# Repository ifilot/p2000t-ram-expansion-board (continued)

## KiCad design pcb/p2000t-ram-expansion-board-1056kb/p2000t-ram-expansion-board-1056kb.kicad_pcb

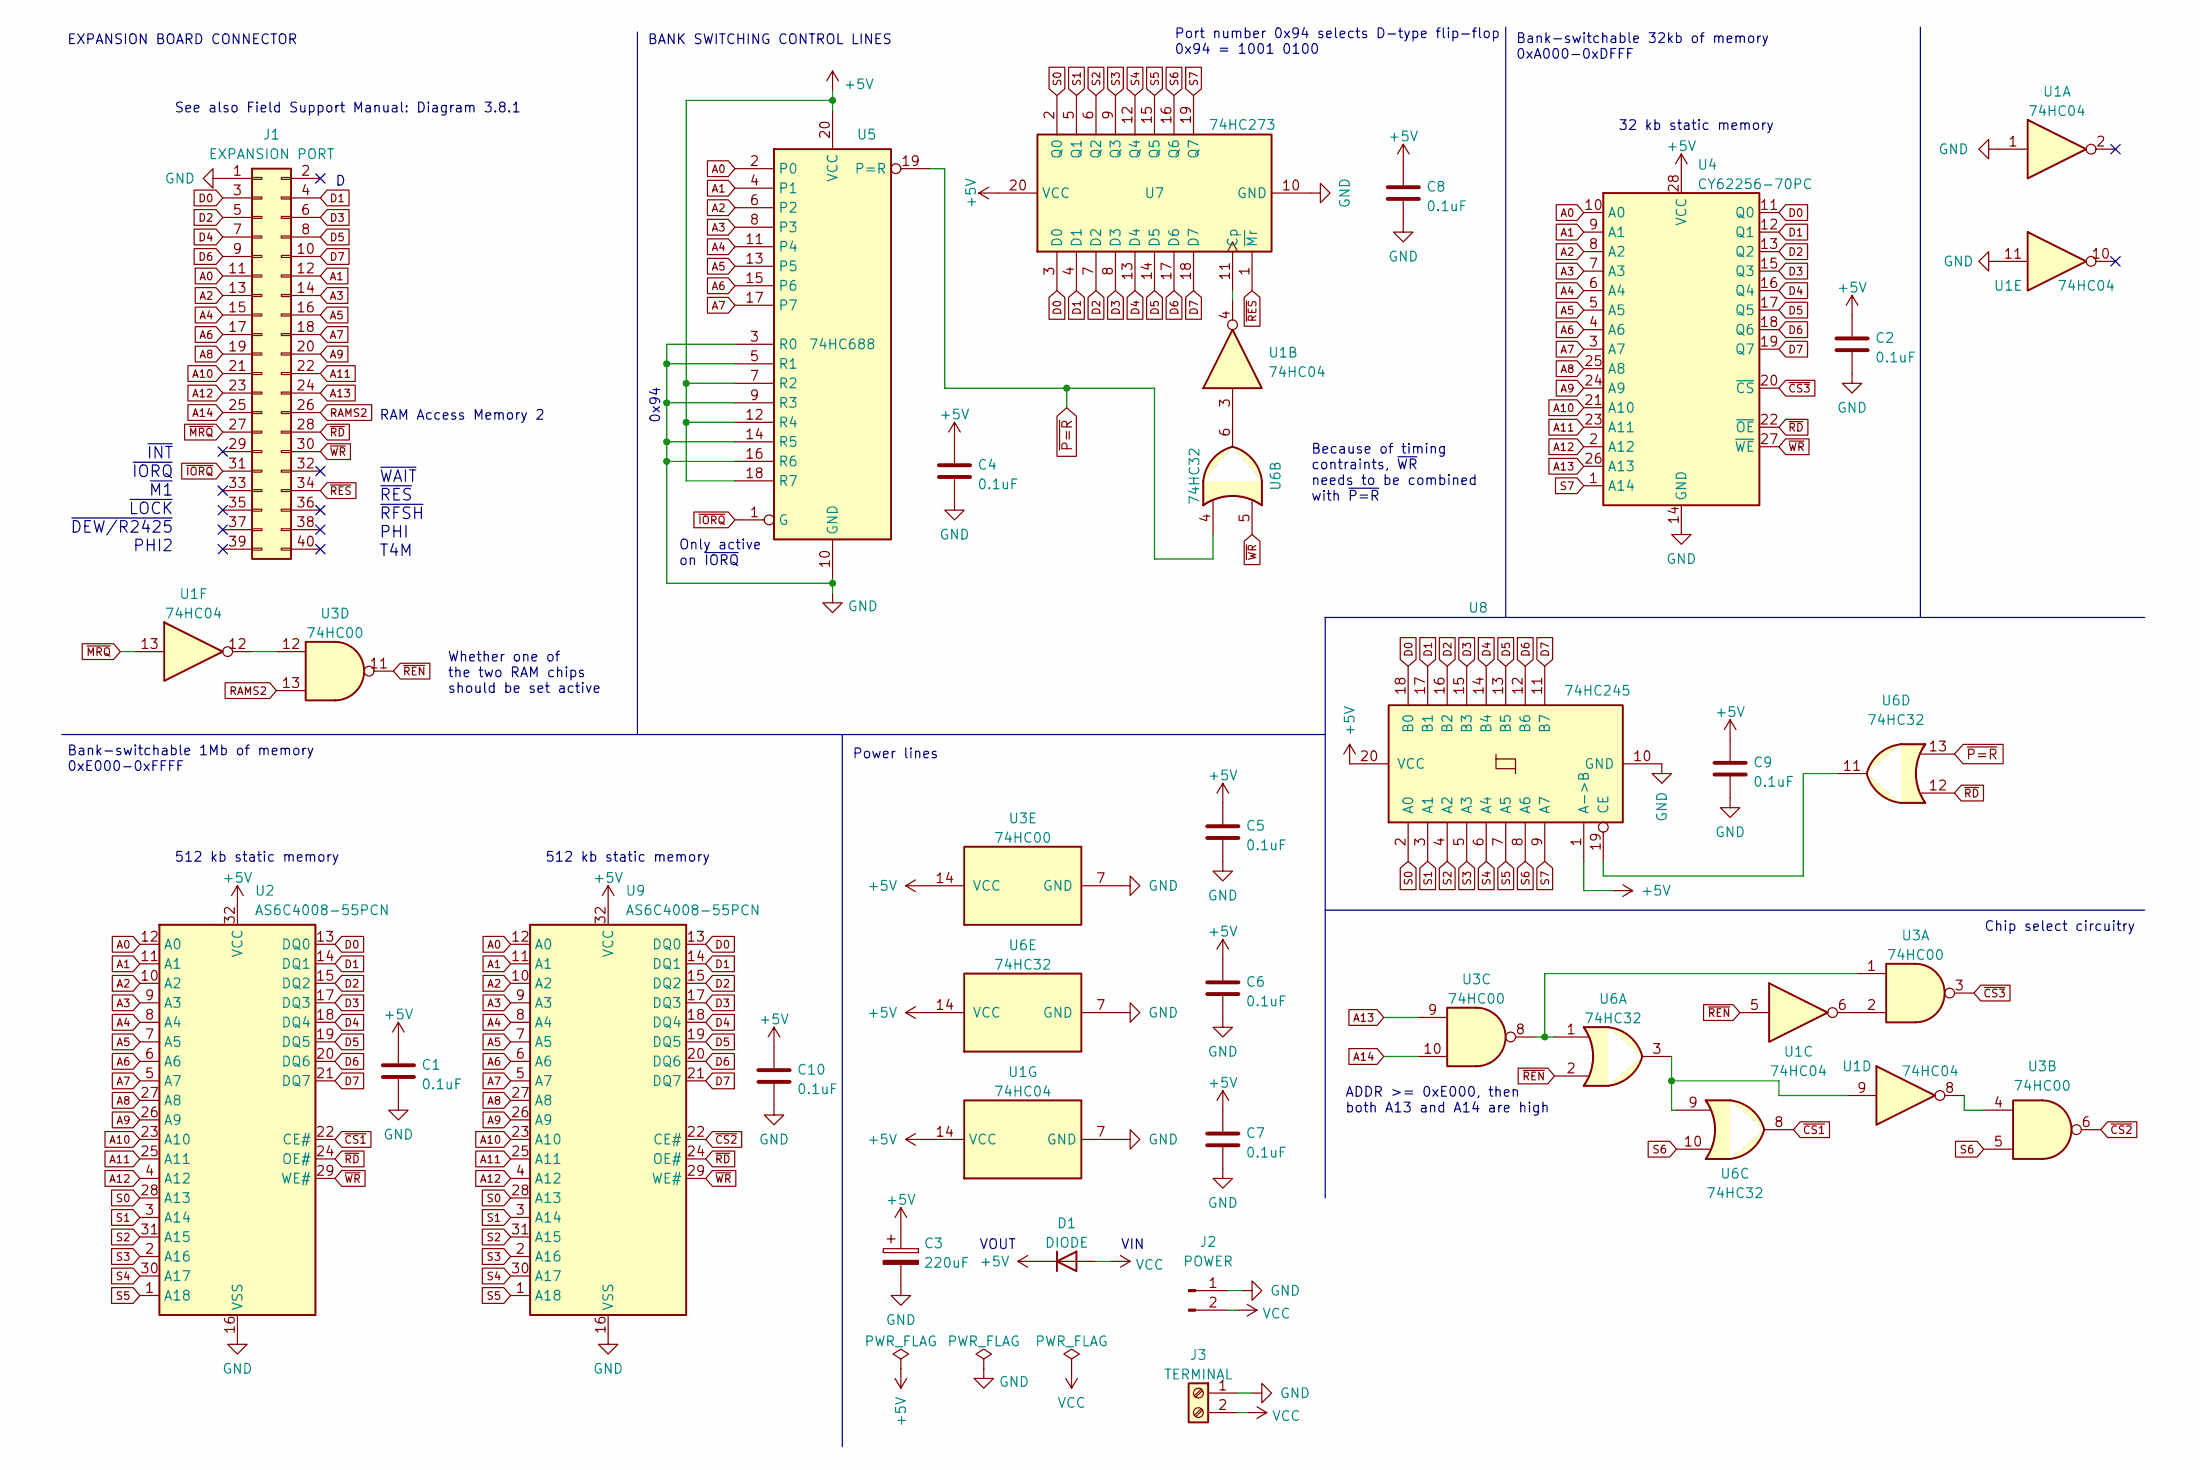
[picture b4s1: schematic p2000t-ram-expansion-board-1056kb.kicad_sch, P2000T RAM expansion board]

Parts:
C1, C2, C4, C5, C6, C7, C8, C9, C10: 0.1uF; C_Disc_D5.0mm_W2.5mm_P5.00mm
C3: 220uF; CP_Radial_D6.3mm_P2.50mm
D1: DIODE; D_DO-35_SOD27_P7.62mm_Horizontal
J1: EXPANSION PORT; PinHeader_2x20_P2.54mm_Vertical
J2: POWER; PinHeader_1x02_P2.54mm_Vertical
J3: TERMINAL; TerminalBlock_bornier-2_P5.08mm
U1: 74HC04; DIP-14_W7.62mm_Socket
U2, U9: AS6C4008-55PCN; DIP-32_W15.24mm_Socket
U3: 74HC00; DIP-14_W7.62mm_Socket
U4: CY62256-70PC; DIP-28_W15.24mm_Socket
U5: 74HC688; DIP-20_W7.62mm_Socket
U6: 74HC32; DIP-14_W7.62mm_Socket
U7: 74HC273; DIP-20_W7.62mm_Socket
U8: 74HC245; DIP-20_W7.62mm_Socket

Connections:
+5V: C1.1, C2.1, C3.1, C4.1, C5.1, C6.1, C7.1, C8.1, C9.1, C10.1, D1.1 (K), U1.14 (VCC), U2.32 (VCC), U3.14 (VCC), U4.28 (VCC), U5.7 (R2), U5.12 (R4), U5.18 (R7), U5.20 (VCC), U6.14 (VCC), U7.20 (VCC), U8.1 (A->B), U8.20 (VCC), U9.32 (VCC)
A0: J1.11, U2.12 (A0), U4.10 (A0), U5.2 (P0), U9.12 (A0)
A1: J1.12, U2.11 (A1), U4.9 (A1), U5.4 (P1), U9.11 (A1)
A2: J1.13, U2.10 (A2), U4.8 (A2), U5.6 (P2), U9.10 (A2)
A3: J1.14, U2.9 (A3), U4.7 (A3), U5.8 (P3), U9.9 (A3)
A4: J1.15, U2.8 (A4), U4.6 (A4), U5.11 (P4), U9.8 (A4)
A5: J1.16, U2.7 (A5), U4.5 (A5), U5.13 (P5), U9.7 (A5)
A6: J1.17, U2.6 (A6), U4.4 (A6), U5.15 (P6), U9.6 (A6)
A7: J1.18, U2.5 (A7), U4.3 (A7), U5.17 (P7), U9.5 (A7)
A8: J1.19, U2.27 (A8), U4.25 (A8), U9.27 (A8)
A9: J1.20, U2.26 (A9), U4.24 (A9), U9.26 (A9)
A10: J1.21, U2.23 (A10), U4.21 (A10), U9.23 (A10)
A11: J1.22, U2.25 (A11), U4.23 (A11), U9.25 (A11)
A12: J1.23, U2.4 (A12), U4.2 (A12), U9.4 (A12)
A13: J1.24, U3.9, U4.26 (A13)
A14: J1.25, U3.10
D0: J1.3, U2.13 (DQ0), U4.11 (Q0), U7.3 (D0), U8.18 (B0), U9.13 (DQ0)
D1: J1.4, U2.14 (DQ1), U4.12 (Q1), U7.4 (D1), U8.17 (B1), U9.14 (DQ1)
D2: J1.5, U2.15 (DQ2), U4.13 (Q2), U7.7 (D2), U8.16 (B2), U9.15 (DQ2)
D3: J1.6, U2.17 (DQ3), U4.15 (Q3), U7.8 (D3), U8.15 (B3), U9.17 (DQ3)
D4: J1.7, U2.18 (DQ4), U4.16 (Q4), U7.13 (D4), U8.14 (B4), U9.18 (DQ4)
D5: J1.8, U2.19 (DQ5), U4.17 (Q5), U7.14 (D5), U8.13 (B5), U9.19 (DQ5)
D6: J1.9, U2.20 (DQ6), U4.18 (Q6), U7.17 (D6), U8.12 (B6), U9.20 (DQ6)
D7: J1.10, U2.21 (DQ7), U4.19 (Q7), U7.18 (D7), U8.11 (B7), U9.21 (DQ7)
GND: C1.2, C2.2, C3.2, C4.2, C5.2, C6.2, C7.2, C8.2, C9.2, C10.2, J1.1, J2.1, J3.1, U1.1, U1.7 (GND), U1.11, U2.16 (VSS), U3.7 (GND), U4.14 (GND), U5.3 (R0), U5.5 (R1), U5.9 (R3), U5.10 (GND), U5.14 (R5), U5.16 (R6), U6.7 (GND), U7.10 (GND), U8.10 (GND), U9.16 (VSS)
unnamed: U1.3, U6.6
unnamed: U1.6, U3.2
unnamed: U1.8, U3.4
unnamed: U1.9, U6.3, U6.9
unnamed: U1.12, U3.12
unnamed: U3.1, U3.8, U6.1
unnamed: U1.4, U7.11 (Cp)
unnamed: U6.11, U8.19 (CE)
RAMS2: J1.26, U3.13
S0: U2.28 (A13), U7.2 (Q0), U8.2 (A0), U9.28 (A13)
S1: U2.3 (A14), U7.5 (Q1), U8.3 (A1), U9.3 (A14)
S2: U2.31 (A15), U7.6 (Q2), U8.4 (A2), U9.31 (A15)
S3: U2.2 (A16), U7.9 (Q3), U8.5 (A3), U9.2 (A16)
S4: U2.30 (A17), U7.12 (Q4), U8.6 (A4), U9.30 (A17)
S5: U2.1 (A18), U7.15 (Q5), U8.7 (A5), U9.1 (A18)
S6: U3.5, U6.10, U7.16 (Q6), U8.8 (A6)
S7: U4.1 (A14), U7.19 (Q7), U8.9 (A7)
VCC: D1.2 (A), J2.2, J3.2
~CS1: U2.22 (CE#), U6.8
~CS2: U3.6, U9.22 (CE#)
~CS3: U3.3, U4.20 (~CS)
~IORQ: J1.31, U5.1 (G)
~MRQ: J1.27, U1.13
~P=R: U5.19 (P=R), U6.4, U6.13
~RD: J1.28, U2.24 (OE#), U4.22 (~OE), U6.12, U9.24 (OE#)
~REN: U1.5, U3.11, U6.2
~RES: J1.34, U7.1 (~Mr)
~WR: J1.30, U2.29 (WE#), U4.27 (~WE), U6.5, U9.29 (WE#)

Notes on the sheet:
512 kb static memory
VIN
EXPANSION BOARD CONNECTOR
0x94
VOUT
32 kb static memory
~{INT} ~{IORQ} ~{M1} ~{LOCK} ~{DEW/R2425} PHI2
Only active on ~{IORQ}
RAM Access Memory 2
Bank-switchable 32kb of memory 0xA000-0xDFFF
Because of timing contraints, ~{WR} needs to be combined with ~{P=R}
Bank-switchable 1Mb of memory 0xE000-0xFFFF
See also Field Support Manual: Diagram 3.8.1
Power lines
Chip select circuitry
BANK SWITCHING CONTROL LINES
ADDR >= 0xE000, then both A13 and A14 are high
~{WAIT} ~{RES} ~{RFSH} PHI T4M
Whether one of the two RAM chips should be set active
Port number 0x94 selects D-type flip-flop 0x94 = 1001 0100

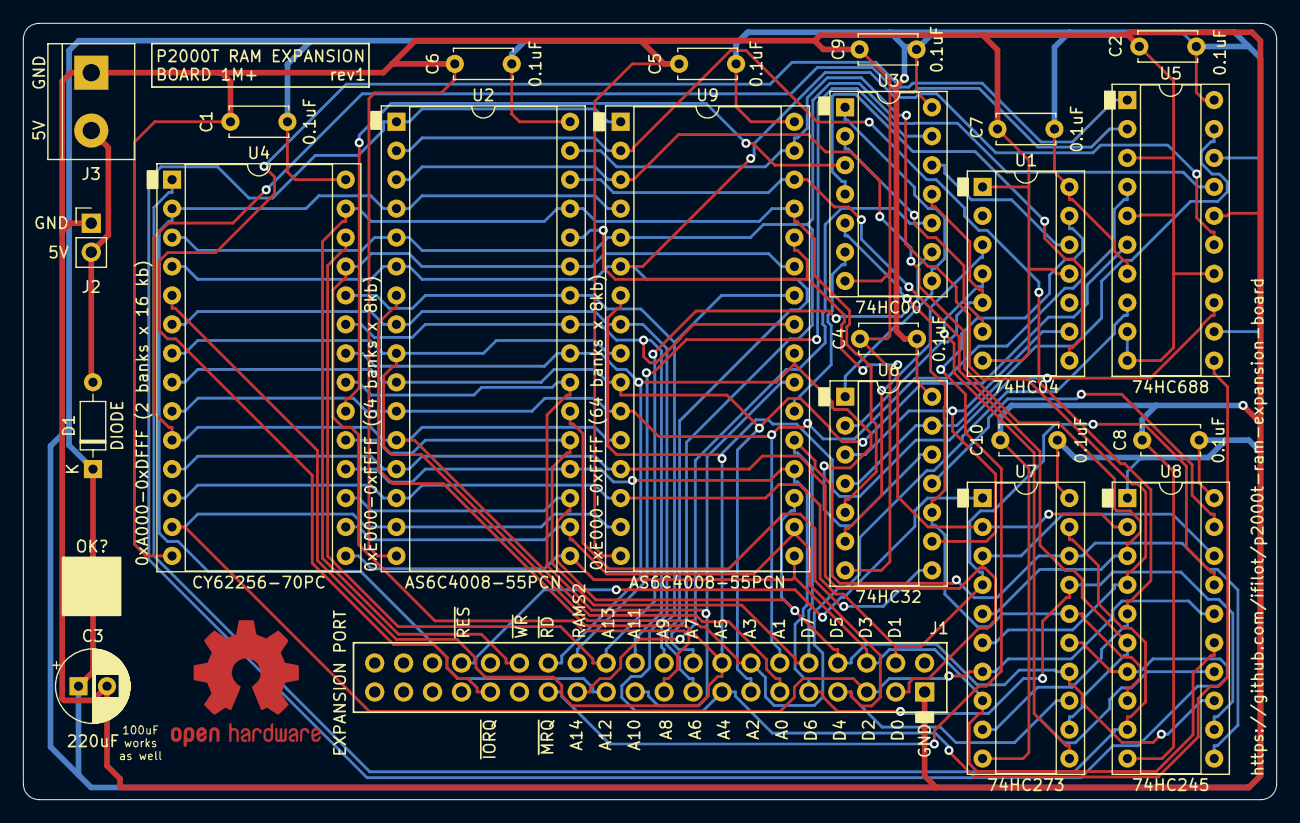
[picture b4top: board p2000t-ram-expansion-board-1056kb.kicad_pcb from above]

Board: 2 copper layers, 110.0 x 68.1 mm, 24 parts (1 on the bottom side), 53 nets.

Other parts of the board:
LOGO1: OSHW-Logo2_14.6x12mm_Copper_AND_Mask

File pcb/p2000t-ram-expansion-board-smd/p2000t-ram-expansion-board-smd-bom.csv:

Comment,Designator,Footprint,LCSC Part #
0.1uF Unpolarized capacitor,"C1,C2,C4,C5,C6,C7,C8,C9,C10",C_0805_2012Metric_Pad1.18x1.45mm_HandSolder,C49678
100uF Polarized capacitor,C3,CP_EIA-3528-21_Kemet-B_Pad1.50x2.35mm_HandSolder,C16133
DIODE Diode,D1,D_SOD-123,C81598
74HC04 Hex Inverter,U1,SOIC-14_3.9x8.7mm_P1.27mm,C5586
"CY62256-70PC 256K (32K x 8) Static RAM, 70ns, DIP-28","U2,U4",TSOP-I-28_11.8x8mm_P0.55mm,C2759940
74HC00 quad 2-input NAND gate,U3,SOIC-14_3.9x8.7mm_P1.27mm,C10090
74HC688 8-bit magnitude comparator,U5,SOIC-20W_7.5x12.8mm_P1.27mm,C88042
74HC32 Quad 2-input OR,U6,SOIC-14_3.9x8.7mm_P1.27mm,C5632
"74HC173 4-bit D-type Register, 3 state out",U7,SOIC-16_3.9x9.9mm_P1.27mm,C546651
"74HC245 Octal BUS Transceivers, 3-State outputs",U8,SOIC-20W_7.5x12.8mm_P1.27mm,C5625
74HC157 Quad 2 to 1 line Multiplexer,U9,SOIC-16_3.9x9.9mm_P1.27mm,C5609

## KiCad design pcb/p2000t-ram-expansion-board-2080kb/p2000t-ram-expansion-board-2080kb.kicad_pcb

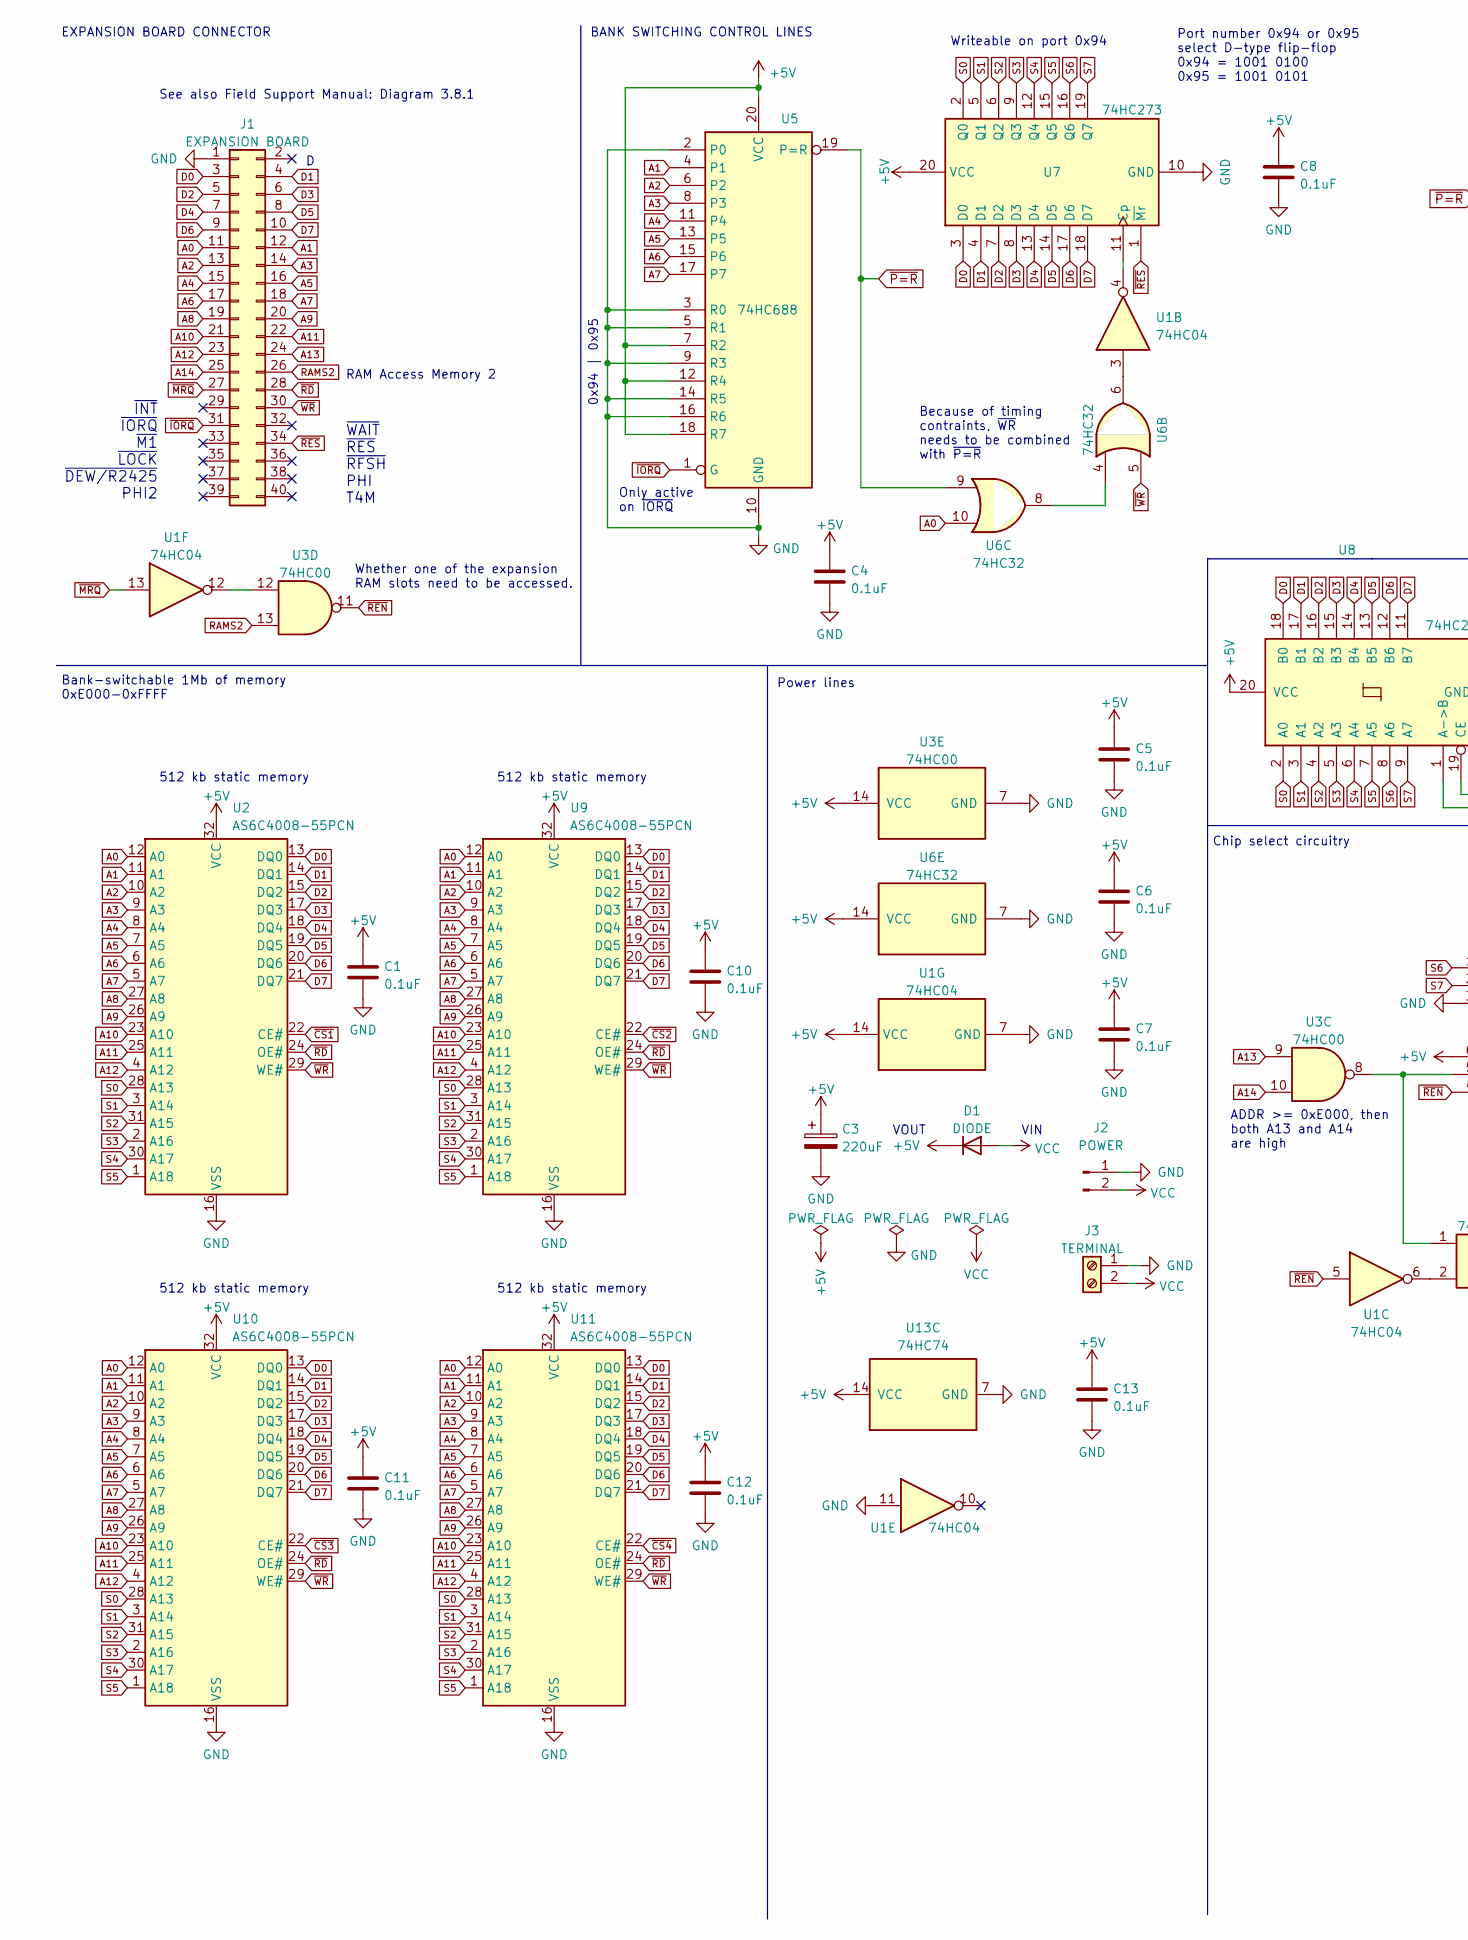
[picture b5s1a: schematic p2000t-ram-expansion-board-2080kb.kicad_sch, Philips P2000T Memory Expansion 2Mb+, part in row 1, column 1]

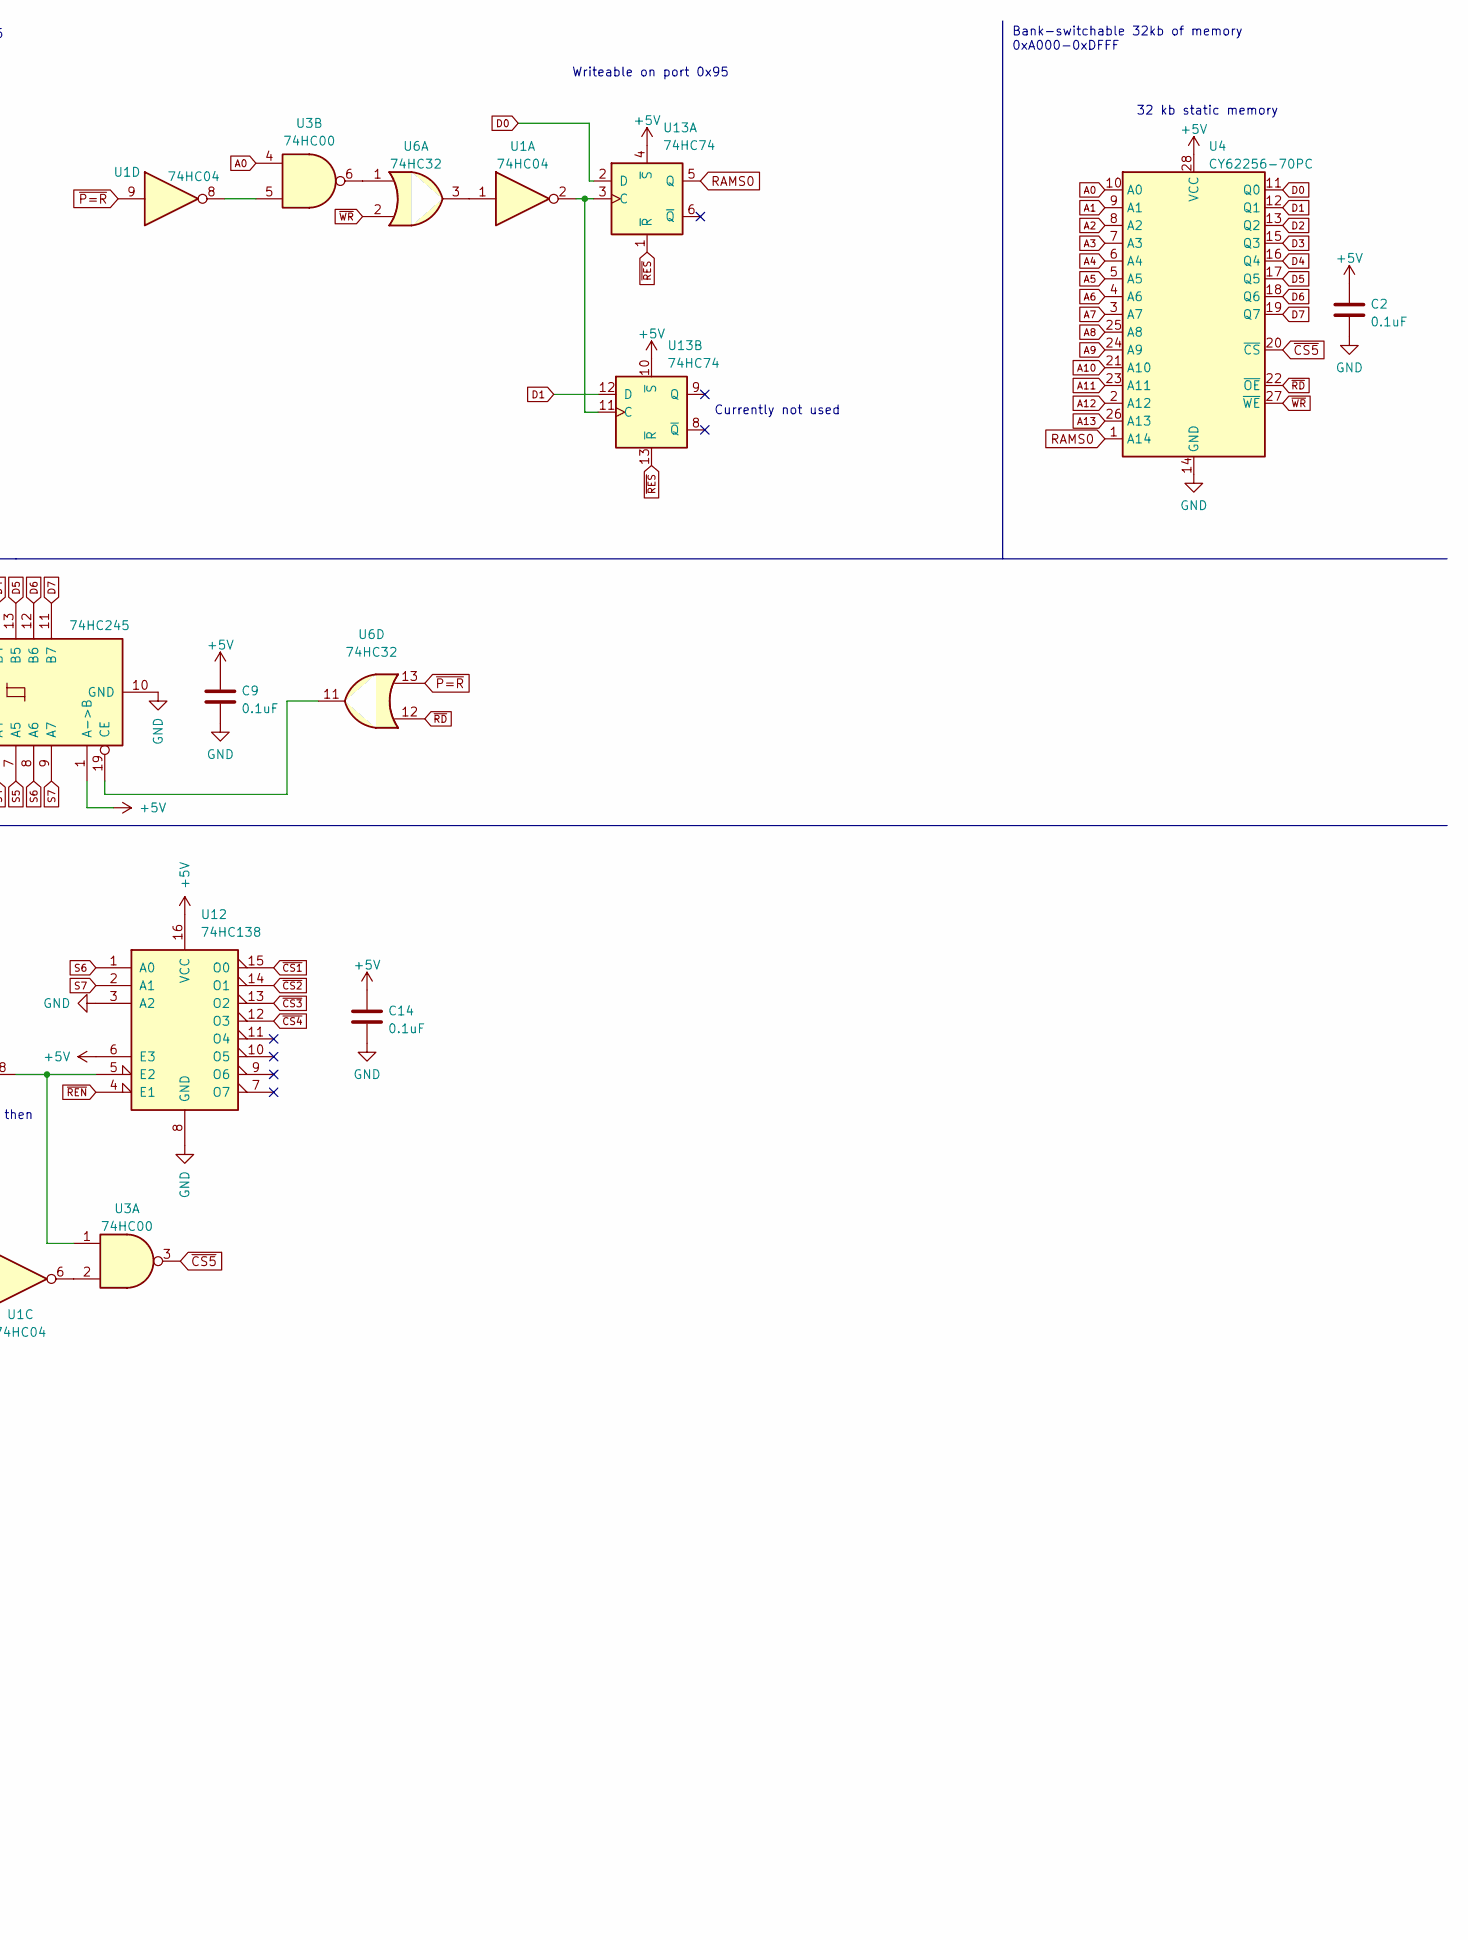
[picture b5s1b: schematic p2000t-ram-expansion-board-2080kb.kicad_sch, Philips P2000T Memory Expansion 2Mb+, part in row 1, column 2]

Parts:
C1, C2, C4, C5, C6, C7, C8, C9, C10, C11, C12, C13, C14: 0.1uF; C_Disc_D5.0mm_W2.5mm_P5.00mm
C3: 220uF; CP_Radial_D6.3mm_P2.50mm
D1: DIODE; D_DO-35_SOD27_P7.62mm_Horizontal
J1: EXPANSION BOARD; PinHeader_2x20_P2.54mm_Vertical
J2: POWER; PinHeader_1x02_P2.54mm_Vertical
J3: TERMINAL; TerminalBlock_bornier-2_P5.08mm
U1: 74HC04; DIP-14_W7.62mm_Socket
U2, U9, U10, U11: AS6C4008-55PCN; DIP-32_W15.24mm_Socket
U3: 74HC00; DIP-14_W7.62mm_Socket
U4: CY62256-70PC; DIP-28_W15.24mm_Socket
U5: 74HC688; DIP-20_W7.62mm_Socket
U6: 74HC32; DIP-14_W7.62mm_Socket
U7: 74HC273; DIP-20_W7.62mm_Socket
U8: 74HC245; DIP-20_W7.62mm_Socket
U12: 74HC138; DIP-16_W7.62mm_Socket
U13: 74HC74; DIP-14_W7.62mm_Socket

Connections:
+5V: C1.1, C2.1, C3.1, C4.1, C5.1, C6.1, C7.1, C8.1, C9.1, C10.1, C11.1, C12.1, C13.1, C14.1, D1.1 (K), U1.14 (VCC), U2.32 (VCC), U3.14 (VCC), U4.28 (VCC), U5.7 (R2), U5.12 (R4), U5.18 (R7), U5.20 (VCC), U6.14 (VCC), U7.20 (VCC), U8.1 (A->B), U8.20 (VCC), U9.32 (VCC), U10.32 (VCC), U11.32 (VCC), U12.6 (E3), U12.16 (VCC), U13.4 (~S), U13.10 (~S), U13.14 (VCC)
A0: J1.11, U2.12 (A0), U3.4, U4.10 (A0), U6.10, U9.12 (A0), U10.12 (A0), U11.12 (A0)
A1: J1.12, U2.11 (A1), U4.9 (A1), U5.4 (P1), U9.11 (A1), U10.11 (A1), U11.11 (A1)
A2: J1.13, U2.10 (A2), U4.8 (A2), U5.6 (P2), U9.10 (A2), U10.10 (A2), U11.10 (A2)
A3: J1.14, U2.9 (A3), U4.7 (A3), U5.8 (P3), U9.9 (A3), U10.9 (A3), U11.9 (A3)
A4: J1.15, U2.8 (A4), U4.6 (A4), U5.11 (P4), U9.8 (A4), U10.8 (A4), U11.8 (A4)
A5: J1.16, U2.7 (A5), U4.5 (A5), U5.13 (P5), U9.7 (A5), U10.7 (A5), U11.7 (A5)
A6: J1.17, U2.6 (A6), U4.4 (A6), U5.15 (P6), U9.6 (A6), U10.6 (A6), U11.6 (A6)
A7: J1.18, U2.5 (A7), U4.3 (A7), U5.17 (P7), U9.5 (A7), U10.5 (A7), U11.5 (A7)
A8: J1.19, U2.27 (A8), U4.25 (A8), U9.27 (A8), U10.27 (A8), U11.27 (A8)
A9: J1.20, U2.26 (A9), U4.24 (A9), U9.26 (A9), U10.26 (A9), U11.26 (A9)
A10: J1.21, U2.23 (A10), U4.21 (A10), U9.23 (A10), U10.23 (A10), U11.23 (A10)
A11: J1.22, U2.25 (A11), U4.23 (A11), U9.25 (A11), U10.25 (A11), U11.25 (A11)
A12: J1.23, U2.4 (A12), U4.2 (A12), U9.4 (A12), U10.4 (A12), U11.4 (A12)
A13: J1.24, U3.9, U4.26 (A13)
A14: J1.25, U3.10
D0: J1.3, U2.13 (DQ0), U4.11 (Q0), U7.3 (D0), U8.18 (B0), U9.13 (DQ0), U10.13 (DQ0), U11.13 (DQ0), U13.2 (D)
D1: J1.4, U2.14 (DQ1), U4.12 (Q1), U7.4 (D1), U8.17 (B1), U9.14 (DQ1), U10.14 (DQ1), U11.14 (DQ1), U13.12 (D)
D2: J1.5, U2.15 (DQ2), U4.13 (Q2), U7.7 (D2), U8.16 (B2), U9.15 (DQ2), U10.15 (DQ2), U11.15 (DQ2)
D3: J1.6, U2.17 (DQ3), U4.15 (Q3), U7.8 (D3), U8.15 (B3), U9.17 (DQ3), U10.17 (DQ3), U11.17 (DQ3)
D4: J1.7, U2.18 (DQ4), U4.16 (Q4), U7.13 (D4), U8.14 (B4), U9.18 (DQ4), U10.18 (DQ4), U11.18 (DQ4)
D5: J1.8, U2.19 (DQ5), U4.17 (Q5), U7.14 (D5), U8.13 (B5), U9.19 (DQ5), U10.19 (DQ5), U11.19 (DQ5)
D6: J1.9, U2.20 (DQ6), U4.18 (Q6), U7.17 (D6), U8.12 (B6), U9.20 (DQ6), U10.20 (DQ6), U11.20 (DQ6)
D7: J1.10, U2.21 (DQ7), U4.19 (Q7), U7.18 (D7), U8.11 (B7), U9.21 (DQ7), U10.21 (DQ7), U11.21 (DQ7)
GND: C1.2, C2.2, C3.2, C4.2, C5.2, C6.2, C7.2, C8.2, C9.2, C10.2, C11.2, C12.2, C13.2, C14.2, J1.1, J2.1, J3.1, U1.7 (GND), U1.11, U2.16 (VSS), U3.7 (GND), U4.14 (GND), U5.2 (P0), U5.3 (R0), U5.5 (R1), U5.9 (R3), U5.10 (GND), U5.14 (R5), U5.16 (R6), U6.7 (GND), U7.10 (GND), U8.10 (GND), U9.16 (VSS), U10.16 (VSS), U11.16 (VSS), U12.3 (A2), U12.8 (GND), U13.7 (GND)
unnamed: U1.1, U6.3
unnamed: U1.3, U6.6
unnamed: U1.6, U3.2
unnamed: U1.8, U3.5
unnamed: U1.12, U3.12
unnamed: U3.6, U6.1
unnamed: U6.4, U6.8
unnamed: U1.4, U7.11 (Cp)
unnamed: U6.11, U8.19 (CE)
unnamed: U3.1, U3.8, U12.5 (E2)
unnamed: U1.2, U13.3 (C), U13.11 (C)
RAMS0: U4.1 (A14), U13.5 (Q)
RAMS2: J1.26, U3.13
S0: U2.28 (A13), U7.2 (Q0), U8.2 (A0), U9.28 (A13), U10.28 (A13), U11.28 (A13)
S1: U2.3 (A14), U7.5 (Q1), U8.3 (A1), U9.3 (A14), U10.3 (A14), U11.3 (A14)
S2: U2.31 (A15), U7.6 (Q2), U8.4 (A2), U9.31 (A15), U10.31 (A15), U11.31 (A15)
S3: U2.2 (A16), U7.9 (Q3), U8.5 (A3), U9.2 (A16), U10.2 (A16), U11.2 (A16)
S4: U2.30 (A17), U7.12 (Q4), U8.6 (A4), U9.30 (A17), U10.30 (A17), U11.30 (A17)
S5: U2.1 (A18), U7.15 (Q5), U8.7 (A5), U9.1 (A18), U10.1 (A18), U11.1 (A18)
S6: U7.16 (Q6), U8.8 (A6), U12.1 (A0)
S7: U7.19 (Q7), U8.9 (A7), U12.2 (A1)
VCC: D1.2 (A), J2.2, J3.2
~CS1: U2.22 (CE#), U12.15 (O0)
~CS2: U9.22 (CE#), U12.14 (O1)
~CS3: U10.22 (CE#), U12.13 (O2)
~CS4: U11.22 (CE#), U12.12 (O3)
~CS5: U3.3, U4.20 (~CS)
~IORQ: J1.31, U5.1 (G)
~MRQ: J1.27, U1.13
~P=R: U1.9, U5.19 (P=R), U6.9, U6.13
~RD: J1.28, U2.24 (OE#), U4.22 (~OE), U6.12, U9.24 (OE#), U10.24 (OE#), U11.24 (OE#)
~REN: U1.5, U3.11, U12.4 (E1)
~RES: J1.34, U7.1 (~Mr), U13.1 (~R), U13.13 (~R)
~WR: J1.30, U2.29 (WE#), U4.27 (~WE), U6.2, U6.5, U9.29 (WE#), U10.29 (WE#), U11.29 (WE#)

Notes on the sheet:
512 kb static memory
VIN
EXPANSION BOARD CONNECTOR
0x94 | 0x95
VOUT
32 kb static memory
~{INT} ~{IORQ} ~{M1} ~{LOCK} ~{DEW/R2425} PHI2
Only active on ~{IORQ}
Writeable on port 0x95
RAM Access Memory 2
Currently not used
Bank-switchable 32kb of memory 0xA000-0xDFFF
Because of timing contraints, ~{WR} needs to be combined with ~{P=R}
Bank-switchable 1Mb of memory 0xE000-0xFFFF
See also Field Support Manual: Diagram 3.8.1
Power lines
Chip select circuitry
BANK SWITCHING CONTROL LINES
ADDR >= 0xE000, then both A13 and A14 are high
Writeable on port 0x94
~{WAIT} ~{RES} ~{RFSH} PHI T4M
Whether one of the expansion RAM slots need to be accessed.
Port number 0x94 or 0x95 select D-type flip-flop 0x94 = 1001 0100 0x95 = 1001 0101

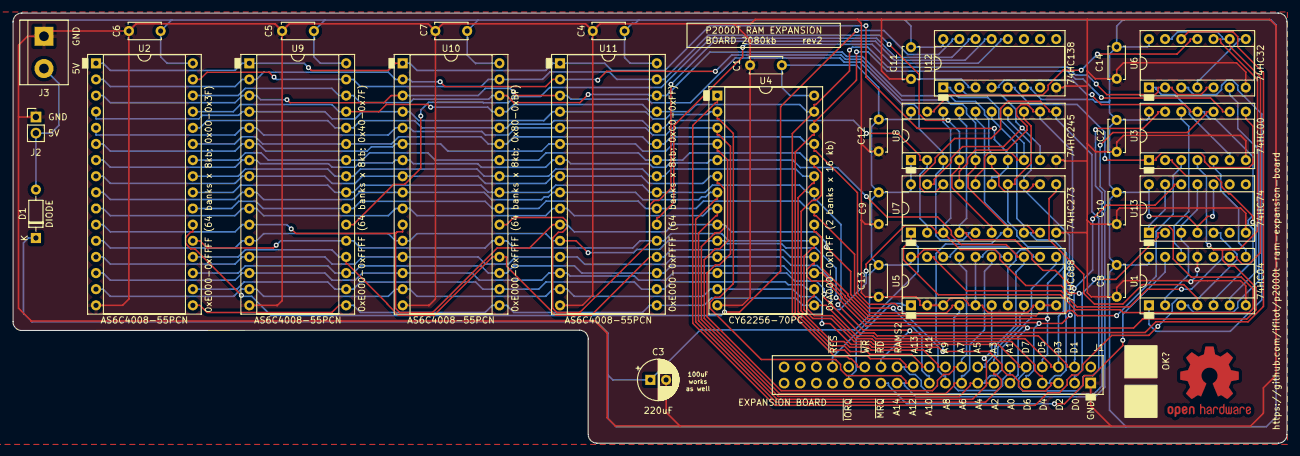
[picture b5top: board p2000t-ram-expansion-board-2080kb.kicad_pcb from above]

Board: 2 copper layers, 200.5 x 67.7 mm, 32 parts (1 on the bottom side), 59 nets.

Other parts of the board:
LOGO1: OSHW-Logo2_14.6x12mm_Copper

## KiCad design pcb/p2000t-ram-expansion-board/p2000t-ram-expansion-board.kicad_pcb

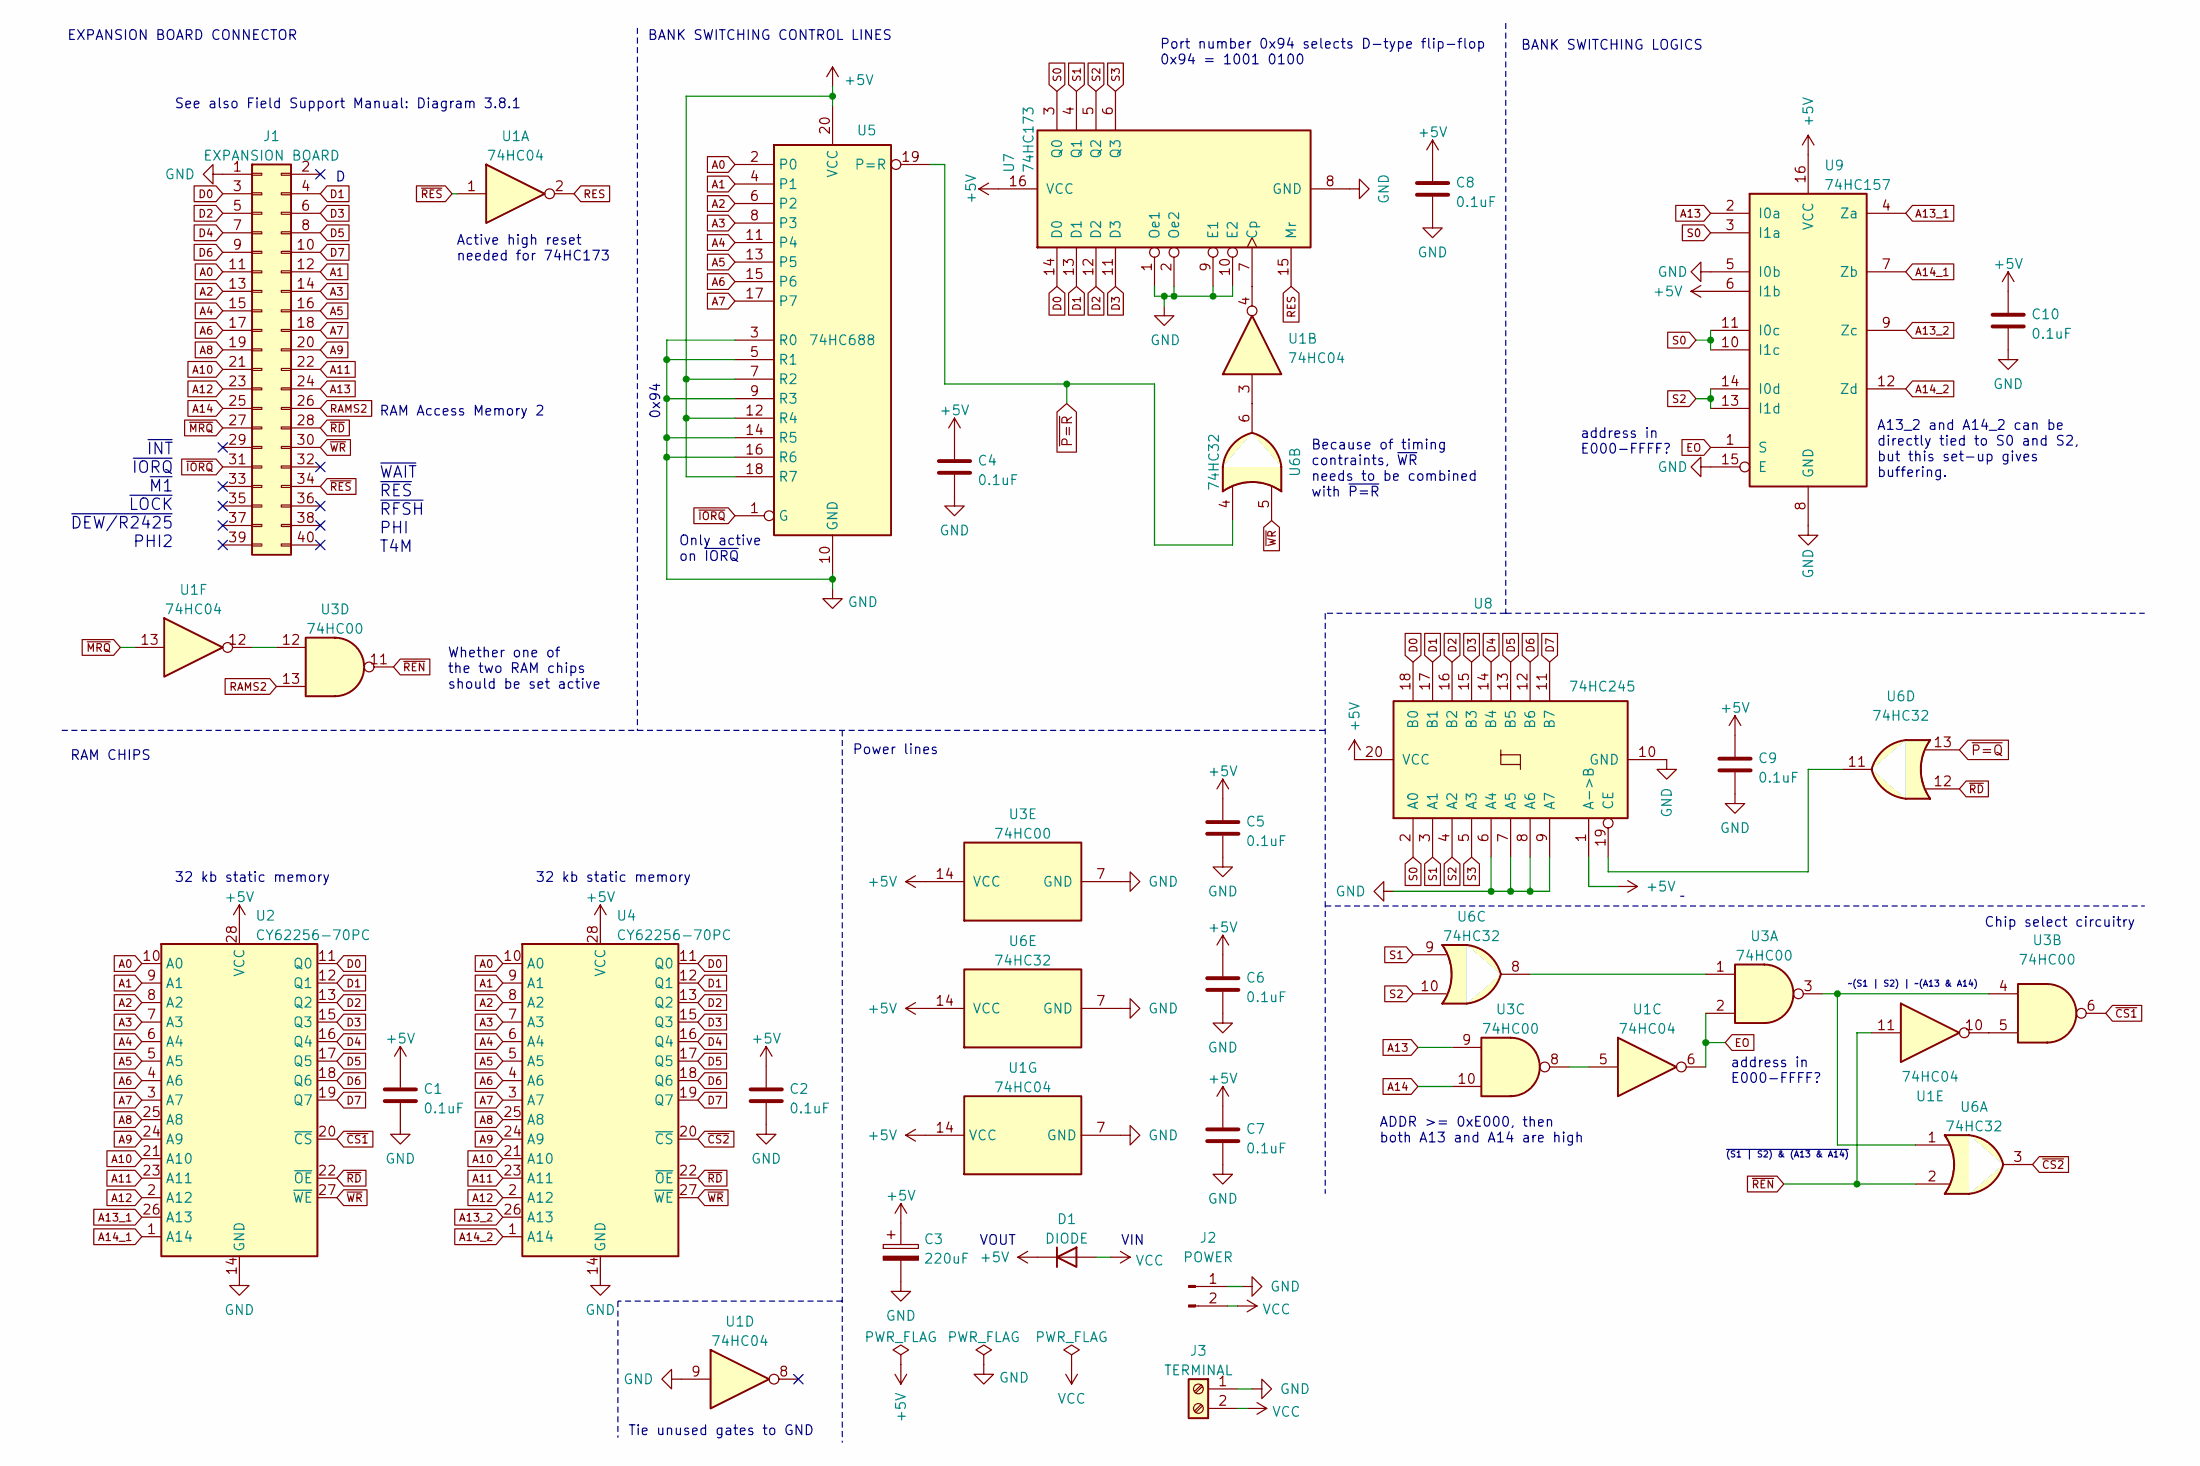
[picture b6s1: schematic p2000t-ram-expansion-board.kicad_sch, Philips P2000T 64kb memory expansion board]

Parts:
C1, C2, C4, C5, C6, C7, C8, C9, C10: 0.1uF; C_Disc_D5.0mm_W2.5mm_P5.00mm
C3: 220uF; CP_Radial_D6.3mm_P2.50mm
D1: DIODE; D_DO-35_SOD27_P7.62mm_Horizontal
J1: EXPANSION BOARD; PinHeader_2x20_P2.54mm_Vertical
J2: POWER; PinHeader_1x02_P2.54mm_Vertical
J3: TERMINAL; TerminalBlock_bornier-2_P5.08mm
U1: 74HC04; DIP-14_W7.62mm_Socket
U2, U4: CY62256-70PC; DIP-28_W15.24mm_Socket
U3: 74HC00; DIP-14_W7.62mm_Socket
U5: 74HC688; DIP-20_W7.62mm_Socket
U6: 74HC32; DIP-14_W7.62mm_Socket
U7: 74HC173; DIP-16_W7.62mm_Socket
U8: 74HC245; DIP-20_W7.62mm_Socket
U9: 74HC157; DIP-16_W7.62mm_Socket

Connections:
+5V: C1.1, C2.1, C3.1, C4.1, C5.1, C6.1, C7.1, C8.1, C9.1, C10.1, D1.1 (K), U1.14 (VCC), U2.28 (VCC), U3.14 (VCC), U4.28 (VCC), U5.7 (R2), U5.12 (R4), U5.18 (R7), U5.20 (VCC), U6.14 (VCC), U7.16 (VCC), U8.1 (A->B), U8.20 (VCC), U9.6 (I1b), U9.16 (VCC)
A0: J1.11, U2.10 (A0), U4.10 (A0), U5.2 (P0)
A1: J1.12, U2.9 (A1), U4.9 (A1), U5.4 (P1)
A2: J1.13, U2.8 (A2), U4.8 (A2), U5.6 (P2)
A3: J1.14, U2.7 (A3), U4.7 (A3), U5.8 (P3)
A4: J1.15, U2.6 (A4), U4.6 (A4), U5.11 (P4)
A5: J1.16, U2.5 (A5), U4.5 (A5), U5.13 (P5)
A6: J1.17, U2.4 (A6), U4.4 (A6), U5.15 (P6)
A7: J1.18, U2.3 (A7), U4.3 (A7), U5.17 (P7)
A8: J1.19, U2.25 (A8), U4.25 (A8)
A9: J1.20, U2.24 (A9), U4.24 (A9)
A10: J1.21, U2.21 (A10), U4.21 (A10)
A11: J1.22, U2.23 (A11), U4.23 (A11)
A12: J1.23, U2.2 (A12), U4.2 (A12)
A13: J1.24, U3.9, U9.2 (I0a)
A13_1: U2.26 (A13), U9.4 (Za)
A13_2: U4.26 (A13), U9.9 (Zc)
A14: J1.25, U3.10
A14_1: U2.1 (A14), U9.7 (Zb)
A14_2: U4.1 (A14), U9.12 (Zd)
D0: J1.3, U2.11 (Q0), U4.11 (Q0), U7.14 (D0), U8.18 (B0)
D1: J1.4, U2.12 (Q1), U4.12 (Q1), U7.13 (D1), U8.17 (B1)
D2: J1.5, U2.13 (Q2), U4.13 (Q2), U7.12 (D2), U8.16 (B2)
D3: J1.6, U2.15 (Q3), U4.15 (Q3), U7.11 (D3), U8.15 (B3)
D4: J1.7, U2.16 (Q4), U4.16 (Q4), U8.14 (B4)
D5: J1.8, U2.17 (Q5), U4.17 (Q5), U8.13 (B5)
D6: J1.9, U2.18 (Q6), U4.18 (Q6), U8.12 (B6)
D7: J1.10, U2.19 (Q7), U4.19 (Q7), U8.11 (B7)
EO: U1.6, U3.2, U9.1 (S)
GND: C1.2, C2.2, C3.2, C4.2, C5.2, C6.2, C7.2, C8.2, C9.2, C10.2, J1.1, J2.1, J3.1, U1.7 (GND), U1.9, U2.14 (GND), U3.7 (GND), U4.14 (GND), U5.3 (R0), U5.5 (R1), U5.9 (R3), U5.10 (GND), U5.14 (R5), U5.16 (R6), U6.7 (GND), U7.1 (Oe1), U7.2 (Oe2), U7.8 (GND), U7.9 (E1), U7.10 (E2), U8.6 (A4), U8.7 (A5), U8.8 (A6), U8.9 (A7), U8.10 (GND), U9.5 (I0b), U9.8 (GND), U9.15 (E)
unnamed: U1.3, U6.6
unnamed: U1.4, U7.7 (Cp)
unnamed: U1.5, U3.8
unnamed: U1.10, U3.5
unnamed: U1.12, U3.12
unnamed: U3.1, U6.8
unnamed: U3.3, U3.4, U6.1
unnamed: U6.11, U8.19 (CE)
RAMS2: J1.26, U3.13
RES: U1.2, U7.15 (Mr)
S0: U7.3 (Q0), U8.2 (A0), U9.3 (I1a), U9.10 (I1c), U9.11 (I0c)
S1: U6.9, U7.4 (Q1), U8.3 (A1)
S2: U6.10, U7.5 (Q2), U8.4 (A2), U9.13 (I1d), U9.14 (I0d)
S3: U7.6 (Q3), U8.5 (A3)
VCC: D1.2 (A), J2.2, J3.2
~CS1: U2.20 (~CS), U3.6
~CS2: U4.20 (~CS), U6.3
~IORQ: J1.31, U5.1 (G)
~MRQ: J1.27, U1.13
~RD: J1.28, U2.22 (~OE), U4.22 (~OE), U6.12
~REN: U1.11, U3.11, U6.2
~RES: J1.34, U1.1
~WR: J1.30, U2.27 (~WE), U4.27 (~WE), U6.5

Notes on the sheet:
VIN
EXPANSION BOARD CONNECTOR
0x94
VOUT
32 kb static memory
~{INT} ~{IORQ} ~{M1} ~{LOCK} ~{DEW/R2425} PHI2
Only active on ~{IORQ}
RAM Access Memory 2
address in E000-FFFF?
Because of timing contraints, ~{WR} needs to be combined with ~{P=R}
BANK SWITCHING LOGICS
RAM CHIPS
See also Field Support Manual: Diagram 3.8.1
~{(S1 | S2) & (A13 & A14)}
Power lines
Chip select circuitry
BANK SWITCHING CONTROL LINES
Tie unused gates to GND
A13_2 and A14_2 can be directly tied to S0 and S2, but this set-up gives buffering.
ADDR >= 0xE000, then both A13 and A14 are high
~{WAIT} ~{RES} ~{RFSH} PHI T4M
Active high reset needed for 74HC173
Whether one of the two RAM chips should be set active
Port number 0x94 selects D-type flip-flop 0x94 = 1001 0100
~(S1 | S2) | ~(A13 & A14)

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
